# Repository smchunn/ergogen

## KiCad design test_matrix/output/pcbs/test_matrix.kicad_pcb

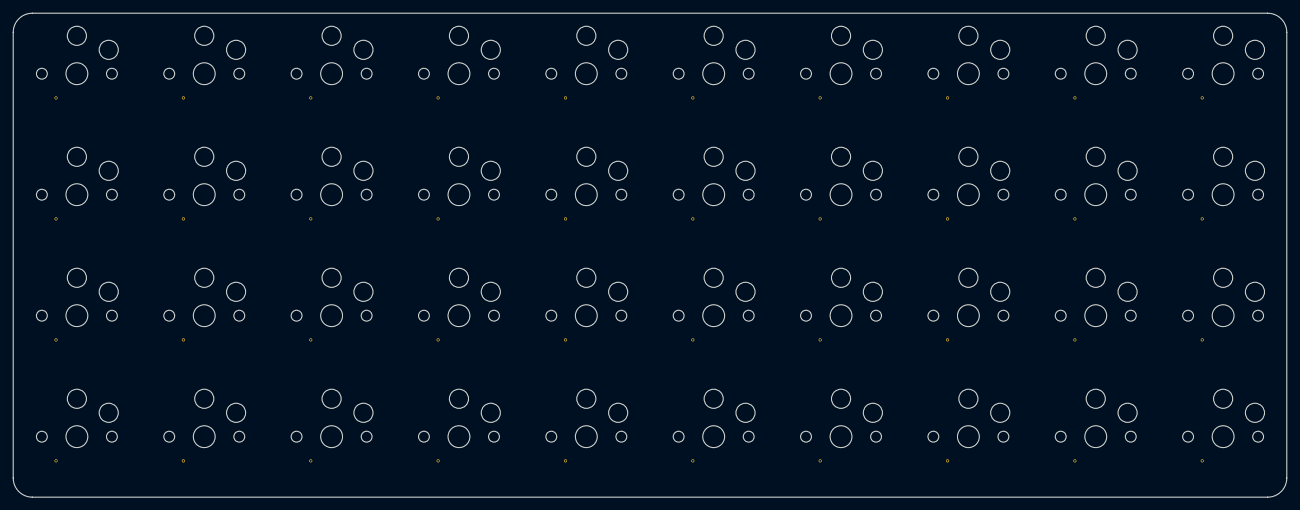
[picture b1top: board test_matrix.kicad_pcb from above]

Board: 2 copper layers, 200.0 x 76.0 mm, 40 parts (0 on the bottom side), 54 nets, no tracks yet.

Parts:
S1, S2, S3, S4, S5, S6, S7, S8, S9, S10, S11, S12, S13, S14, S15, S16, S17, S18, S19, S20, S21, S22, S23, S24, S25, S26, S27, S28, S29, S30, S31, S32, S33, S34, S35, S36, S37, S38, S39, S40: PG1350

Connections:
P4: S1.4, S1.6, S5.4, S5.6, S9.4, S9.6, S13.4, S13.6, S17.4, S17.6, S21.4, S21.6, S25.4, S25.6, S29.4, S29.6, S33.4, S33.6, S37.4, S37.6
P5: S2.4, S2.6, S6.4, S6.6, S10.4, S10.6, S14.4, S14.6, S18.4, S18.6, S22.4, S22.6, S26.4, S26.6, S30.4, S30.6, S34.4, S34.6, S38.4, S38.6
P6: S3.4, S3.6, S7.4, S7.6, S11.4, S11.6, S15.4, S15.6, S19.4, S19.6, S23.4, S23.6, S27.4, S27.6, S31.4, S31.6, S35.4, S35.6, S39.4, S39.6
P7: S4.4, S4.6, S8.4, S8.6, S12.4, S12.6, S16.4, S16.6, S20.4, S20.6, S24.4, S24.6, S28.4, S28.6, S32.4, S32.6, S36.4, S36.6, S40.4, S40.6
P8: S1.2, S2.2, S3.2, S4.2
P9: S5.2, S6.2, S7.2, S8.2
P10: S9.2, S10.2, S11.2, S12.2
P14: S17.2, S18.2, S19.2, S20.2
P15: S21.2, S22.2, S23.2, S24.2
P16: S13.2, S14.2, S15.2, S16.2
P18: S25.2, S26.2, S27.2, S28.2
P19: S29.2, S30.2, S31.2, S32.2
P20: S33.2, S34.2, S35.2, S36.2
P21: S37.2, S38.2, S39.2, S40.2
lindex_bottom: S14.1, S14.3
lindex_home: S15.1, S15.3
lindex_mods: S13.1, S13.3
lindex_top: S16.1, S16.3
linner_bottom: S18.1, S18.3
linner_home: S19.1, S19.3
linner_mods: S17.1, S17.3
linner_top: S20.1, S20.3
lmiddle_bottom: S10.1, S10.3
lmiddle_home: S11.1, S11.3
lmiddle_mods: S9.1, S9.3
lmiddle_top: S12.1, S12.3
lpinky_bottom: S2.1, S2.3
lpinky_home: S3.1, S3.3
lpinky_mods: S1.1, S1.3
lpinky_top: S4.1, S4.3
lring_bottom: S6.1, S6.3
lring_home: S7.1, S7.3
lring_mods: S5.1, S5.3
lring_top: S8.1, S8.3
rindex_bottom: S26.1, S26.3
rindex_home: S27.1, S27.3
rindex_mods: S25.1, S25.3
rindex_top: S28.1, S28.3
rinner_bottom: S22.1, S22.3
rinner_home: S23.1, S23.3
rinner_mods: S21.1, S21.3
rinner_top: S24.1, S24.3
rmiddle_bottom: S30.1, S30.3
rmiddle_home: S31.1, S31.3
rmiddle_mods: S29.1, S29.3
rmiddle_top: S32.1, S32.3
rpinky_bottom: S38.1, S38.3
rpinky_home: S39.1, S39.3
rpinky_mods: S37.1, S37.3
rpinky_top: S40.1, S40.3
rring_bottom: S34.1, S34.3
rring_home: S35.1, S35.3
rring_mods: S33.1, S33.3
rring_top: S36.1, S36.3

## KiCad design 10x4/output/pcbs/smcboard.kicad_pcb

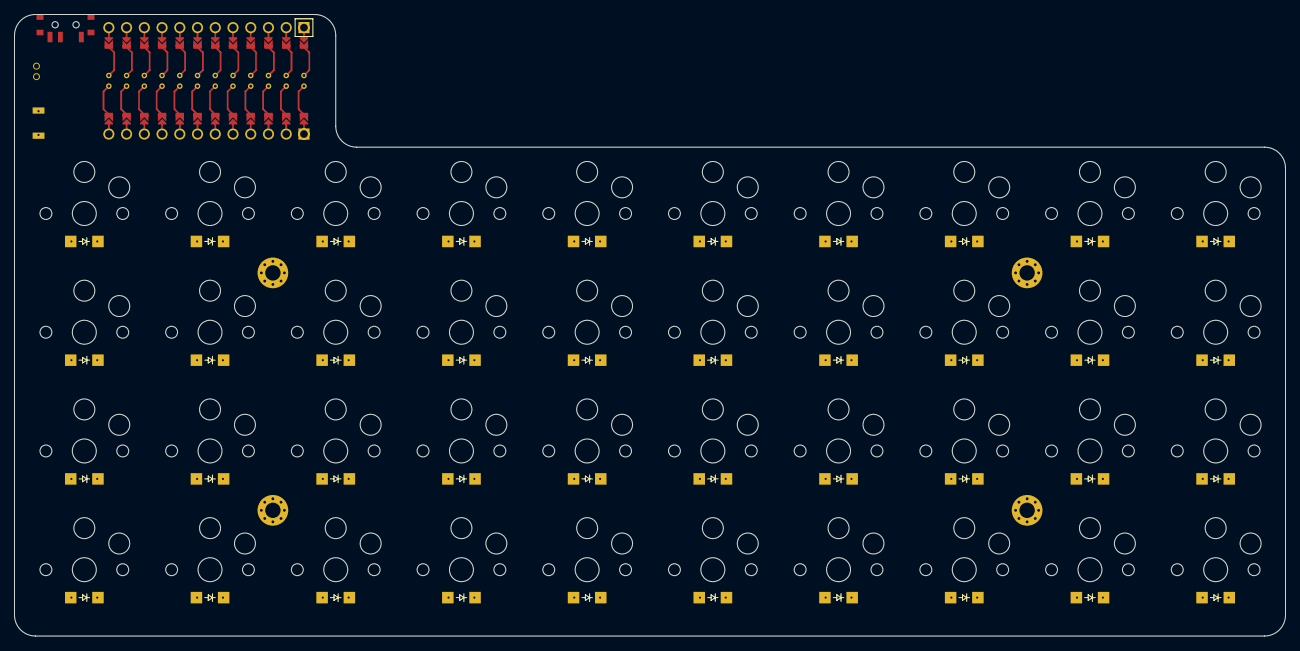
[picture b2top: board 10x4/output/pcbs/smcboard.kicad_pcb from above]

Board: 2 copper layers, 182.0 x 89.0 mm, 85 parts (0 on the bottom side), 55 nets, no tracks yet.

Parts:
D1, D2, D3, D4, D5, D6, D7, D8, D9, D10, D11, D12, D13, D14, D15, D16, D17, D18, D19, D20, D21, D22, D23, D24, D25, D26, D27, D28, D29, D30, D31, D32, D33, D34, D35, D36, D37, D38, D39, D40: ComboDiode
MCU1: ProMicro
S1, S2, S3, S4, S5, S6, S7, S8, S9, S10, S11, S12, S13, S14, S15, S16, S17, S18, S19, S20, S21, S22, S23, S24, S25, S26, S27, S28, S29, S30, S31, S32, S33, S34, S35, S36, S37, S38, S39, S40: PG1350
_4, _5, _6, _7: MountingHole_2.2mm_M2_Pad_Via

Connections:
GND: MCU1.2, MCU1.21, MCU1.22
P4: D1.1, D5.1, D9.1, D13.1, D17.1, D21.1, D25.1, D29.1, D33.1, D37.1, MCU1.18
P5: D2.1, D6.1, D10.1, D14.1, D18.1, D22.1, D26.1, D30.1, D34.1, D38.1, MCU1.17
P6: D3.1, D7.1, D11.1, D15.1, D19.1, D23.1, D27.1, D31.1, D35.1, D39.1, MCU1.16
P7: D4.1, D8.1, D12.1, D16.1, D20.1, D24.1, D28.1, D32.1, D36.1, D40.1, MCU1.15
P8: MCU1.14, S1.2, S2.2, S3.2, S4.2
P9: MCU1.13, S5.2, S6.2, S7.2, S8.2
P10: MCU1.12, S9.2, S10.2, S11.2, S12.2
P14: MCU1.10, S17.2, S18.2, S19.2, S20.2
P15: MCU1.9, S21.2, S22.2, S23.2, S24.2
P16: MCU1.11, S13.2, S14.2, S15.2, S16.2
P18: MCU1.8, S25.2, S26.2, S27.2, S28.2
P19: MCU1.7, S29.2, S30.2, S31.2, S32.2
P20: MCU1.6, S33.2, S34.2, S35.2, S36.2
P21: MCU1.5, S37.2, S38.2, S39.2, S40.2
lindex_bottom: D14.2, S14.1
lindex_home: D15.2, S15.1
lindex_mods: D13.2, S13.1
lindex_top: D16.2, S16.1
linner_bottom: D18.2, S18.1
linner_home: D19.2, S19.1
linner_mods: D17.2, S17.1
linner_top: D20.2, S20.1
lmiddle_bottom: D10.2, S10.1
lmiddle_home: D11.2, S11.1
lmiddle_mods: D9.2, S9.1
lmiddle_top: D12.2, S12.1
lpinky_bottom: D2.2, S2.1
lpinky_home: D3.2, S3.1
lpinky_mods: D1.2, S1.1
lpinky_top: D4.2, S4.1
lring_bottom: D6.2, S6.1
lring_home: D7.2, S7.1
lring_mods: D5.2, S5.1
lring_top: D8.2, S8.1
rindex_bottom: D26.2, S26.1
rindex_home: D27.2, S27.1
rindex_mods: D25.2, S25.1
rindex_top: D28.2, S28.1
rinner_bottom: D22.2, S22.1
rinner_home: D23.2, S23.1
rinner_mods: D21.2, S21.1
rinner_top: D24.2, S24.1
rmiddle_bottom: D30.2, S30.1
rmiddle_home: D31.2, S31.1
rmiddle_mods: D29.2, S29.1
rmiddle_top: D32.2, S32.1
rpinky_bottom: D38.2, S38.1
rpinky_home: D39.2, S39.1
rpinky_mods: D37.2, S37.1
rpinky_top: D40.2, S40.1
rring_bottom: D34.2, S34.1
rring_home: D35.2, S35.1
rring_mods: D33.2, S33.1
rring_top: D36.2, S36.1

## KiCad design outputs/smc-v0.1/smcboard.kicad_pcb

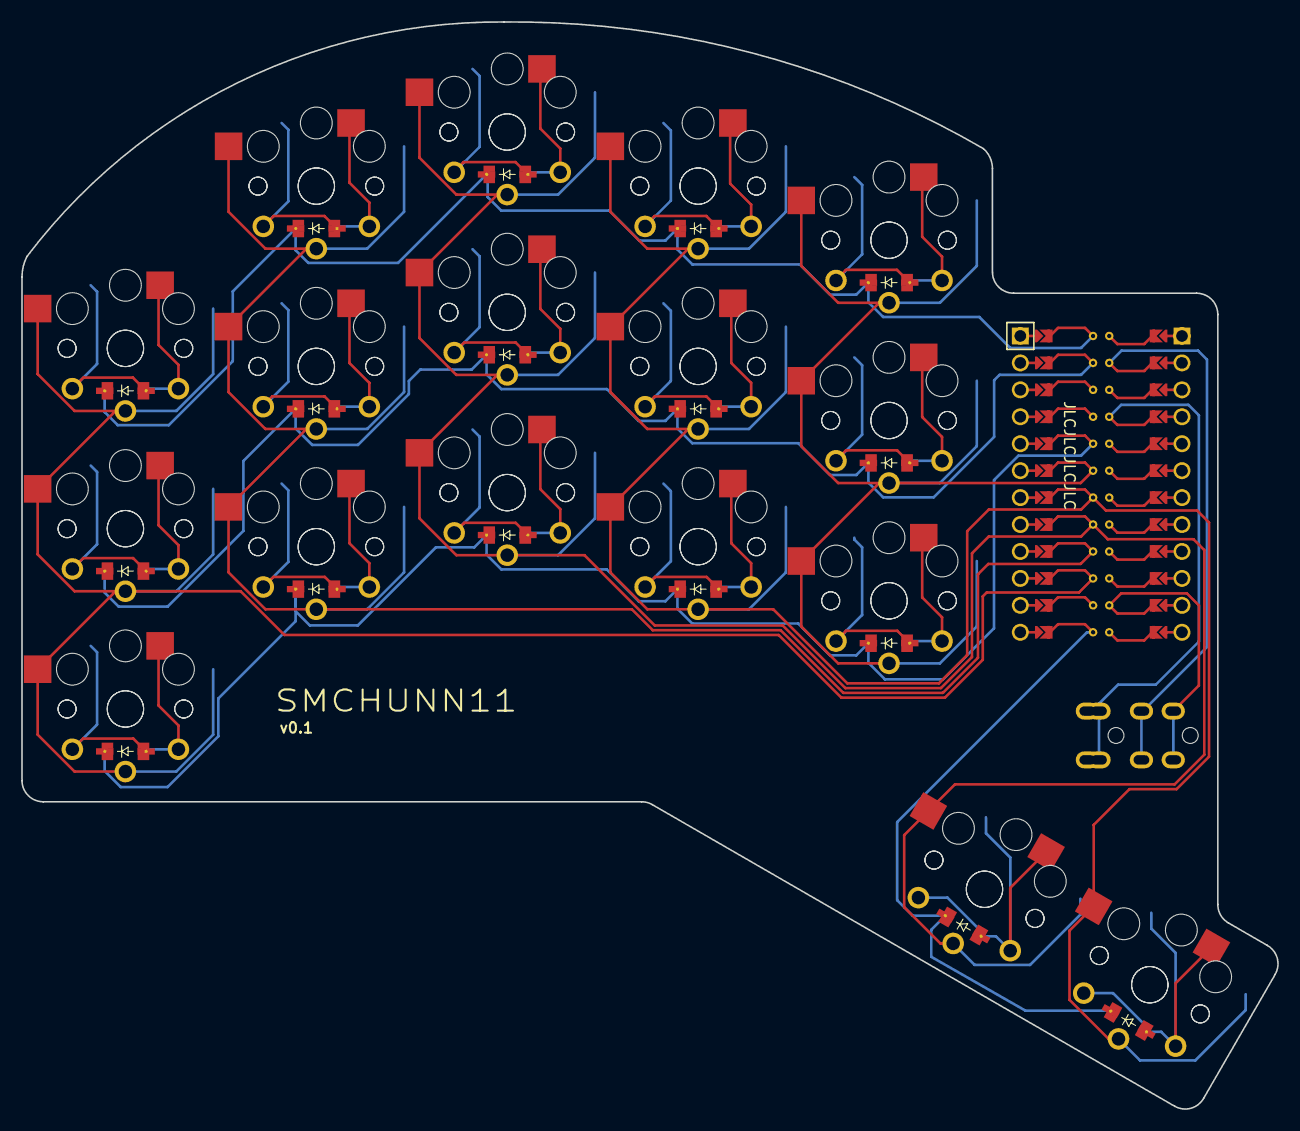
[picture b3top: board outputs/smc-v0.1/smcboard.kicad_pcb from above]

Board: 2 copper layers, 118.4 x 102.5 mm, 52 parts (0 on the bottom side), 27 nets.

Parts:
D1, D2, D3, D4, D5, D6, D7, D8, D9, D10, D11, D12, D13, D14, D15, D16, D17: ComboDiode
MCU1: ProMicro
S1, S2, S3, S4, S5, S6, S7, S8, S9, S10, S11, S12, S13, S14, S15, S16, S17, S18, S19, S20, S21, S22, S23, S24, S25, S26, S27, S28, S29, S30, S31, S32, S33, S34: PG1350

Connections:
GND: MCU1.2, MCU1.21, MCU1.22
P0: D2.1, D5.1, D8.1, D11.1, D14.1, MCU1.23
P1: D3.1, D6.1, D9.1, D12.1, D15.1, MCU1.24
P2: D1.1, D4.1, D7.1, D10.1, D13.1, MCU1.20
P3: MCU1.19, S25.2, S26.2, S27.2, S28.2, S29.2, S30.2
P4: MCU1.18, S19.2, S20.2, S21.2, S22.2, S23.2, S24.2, S33.2, S34.2
P5: MCU1.17, S13.2, S14.2, S15.2, S16.2, S17.2, S18.2, S31.2, S32.2
P6: MCU1.16, S7.2, S8.2, S9.2, S10.2, S11.2, S12.2
P7: MCU1.15, S1.2, S2.2, S3.2, S4.2, S5.2, S6.2
P9: D16.1, D17.1, MCU1.13
home_thumb: D17.2, S33.1, S34.1
index_bottom: D10.2, S19.1, S20.1
index_home: D11.2, S21.1, S22.1
index_top: D12.2, S23.1, S24.1
inner_bottom: D13.2, S25.1, S26.1
inner_home: D14.2, S27.1, S28.1
inner_top: D15.2, S29.1, S30.1
middle_bottom: D7.2, S13.1, S14.1
middle_home: D8.2, S15.1, S16.1
middle_top: D9.2, S17.1, S18.1
near_thumb: D16.2, S31.1, S32.1
pinky_bottom: D1.2, S1.1, S2.1
pinky_home: D2.2, S3.1, S4.1
pinky_top: D3.2, S5.1, S6.1
ring_bottom: D4.2, S7.1, S8.1
ring_home: D5.2, S9.1, S10.1
ring_top: D6.2, S11.1, S12.1

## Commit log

2023-05-09 import files to repo
2024-01-12 update footprints
2025-06-02 mono update
2025-06-02 remove broken sym links
